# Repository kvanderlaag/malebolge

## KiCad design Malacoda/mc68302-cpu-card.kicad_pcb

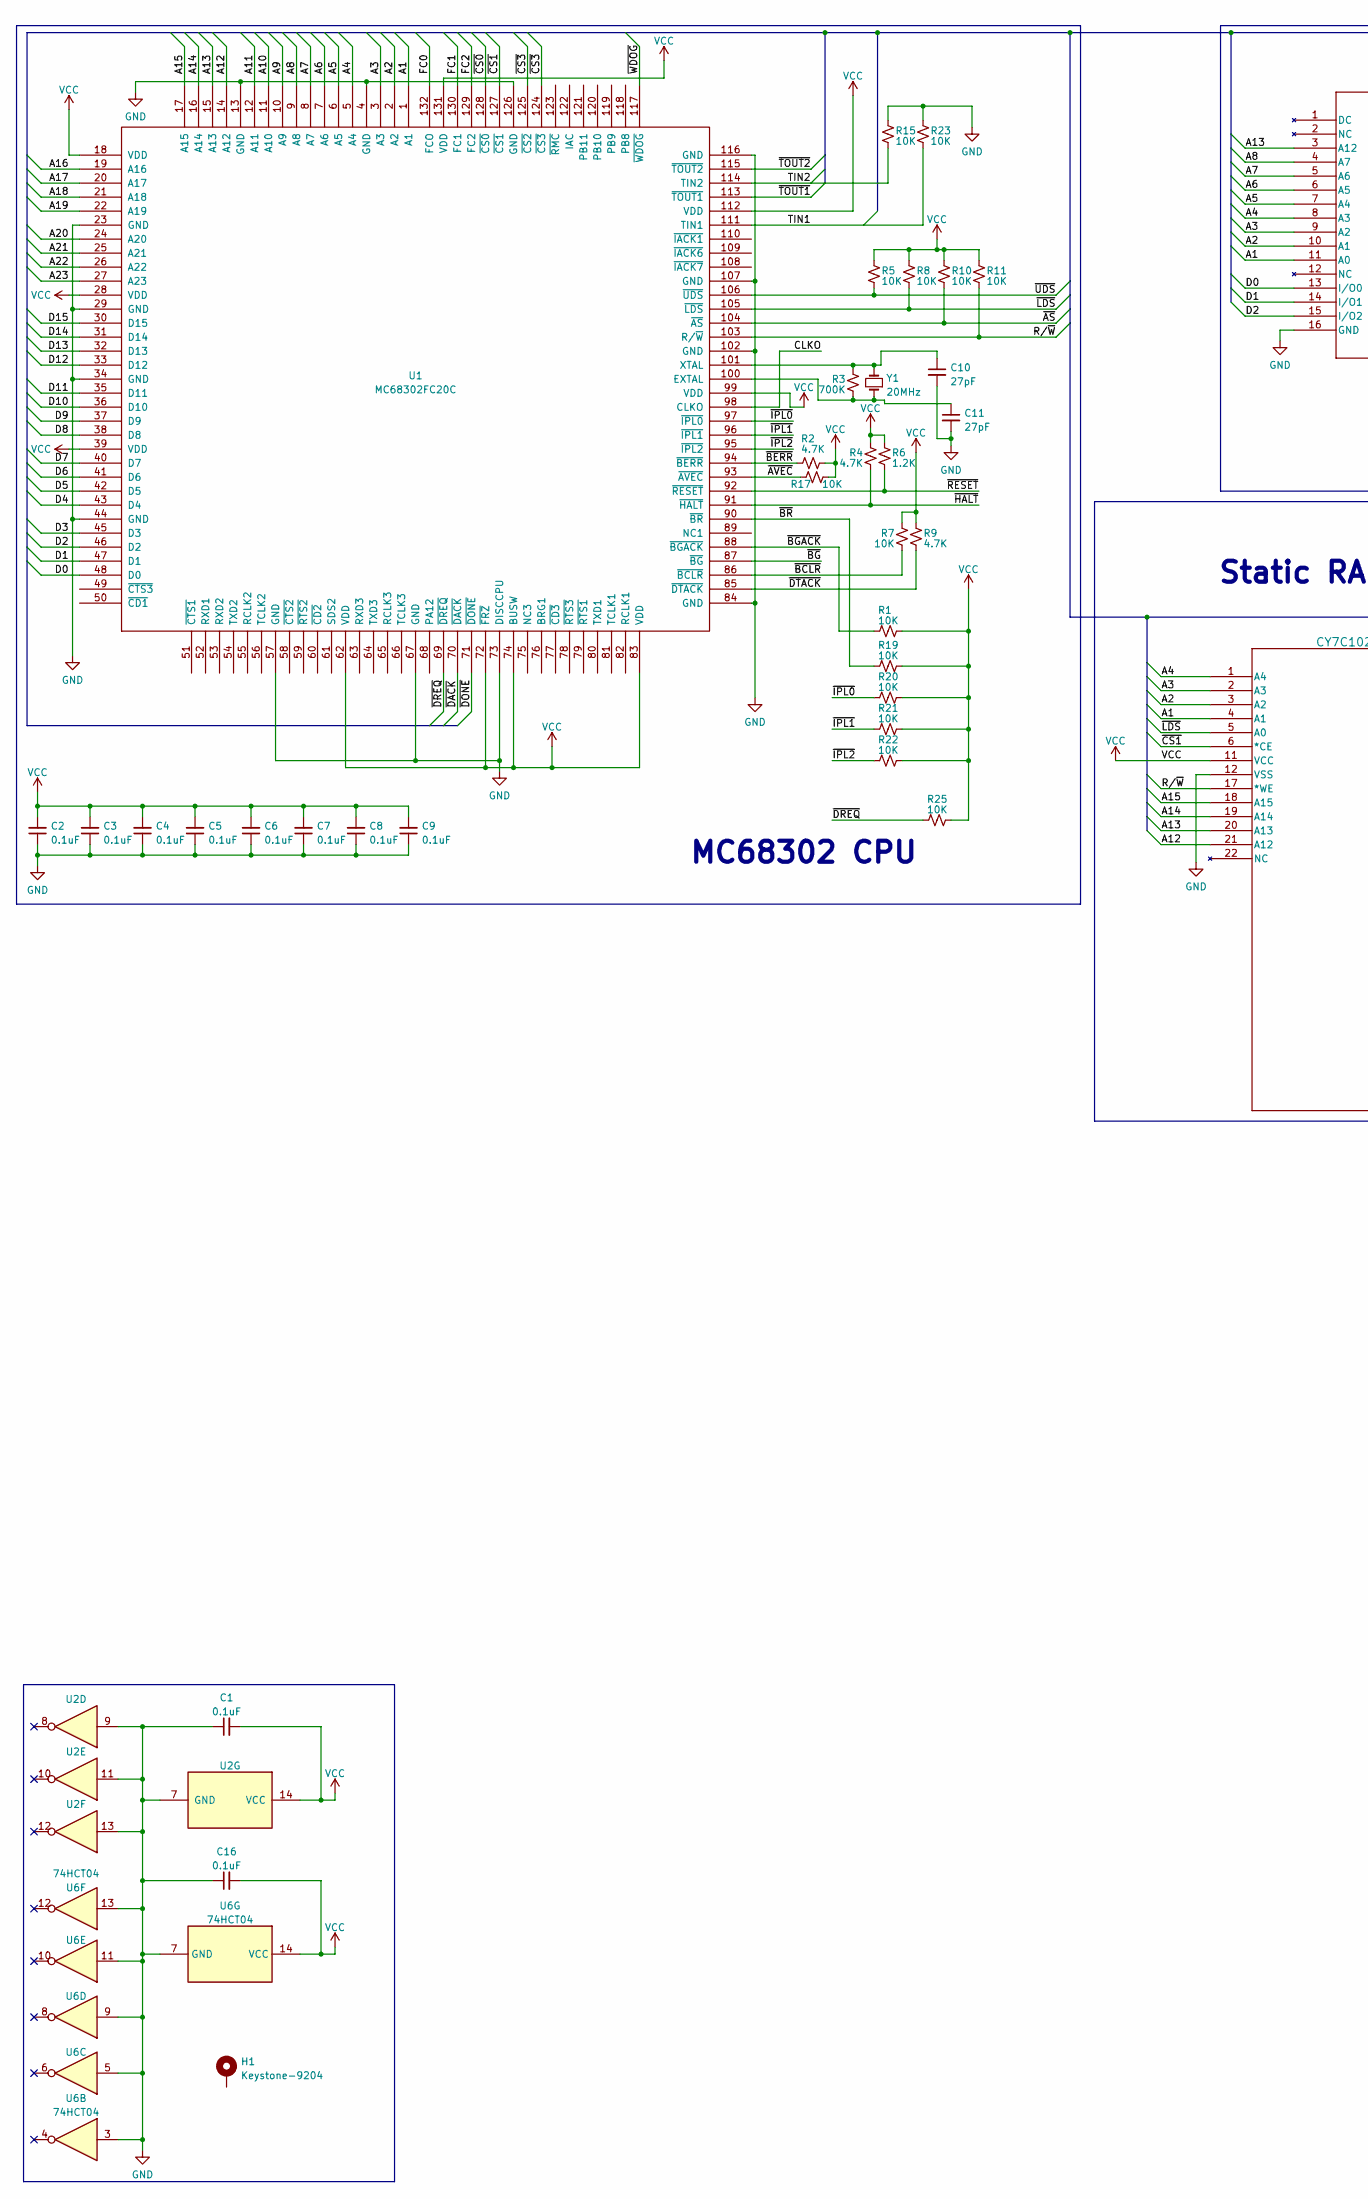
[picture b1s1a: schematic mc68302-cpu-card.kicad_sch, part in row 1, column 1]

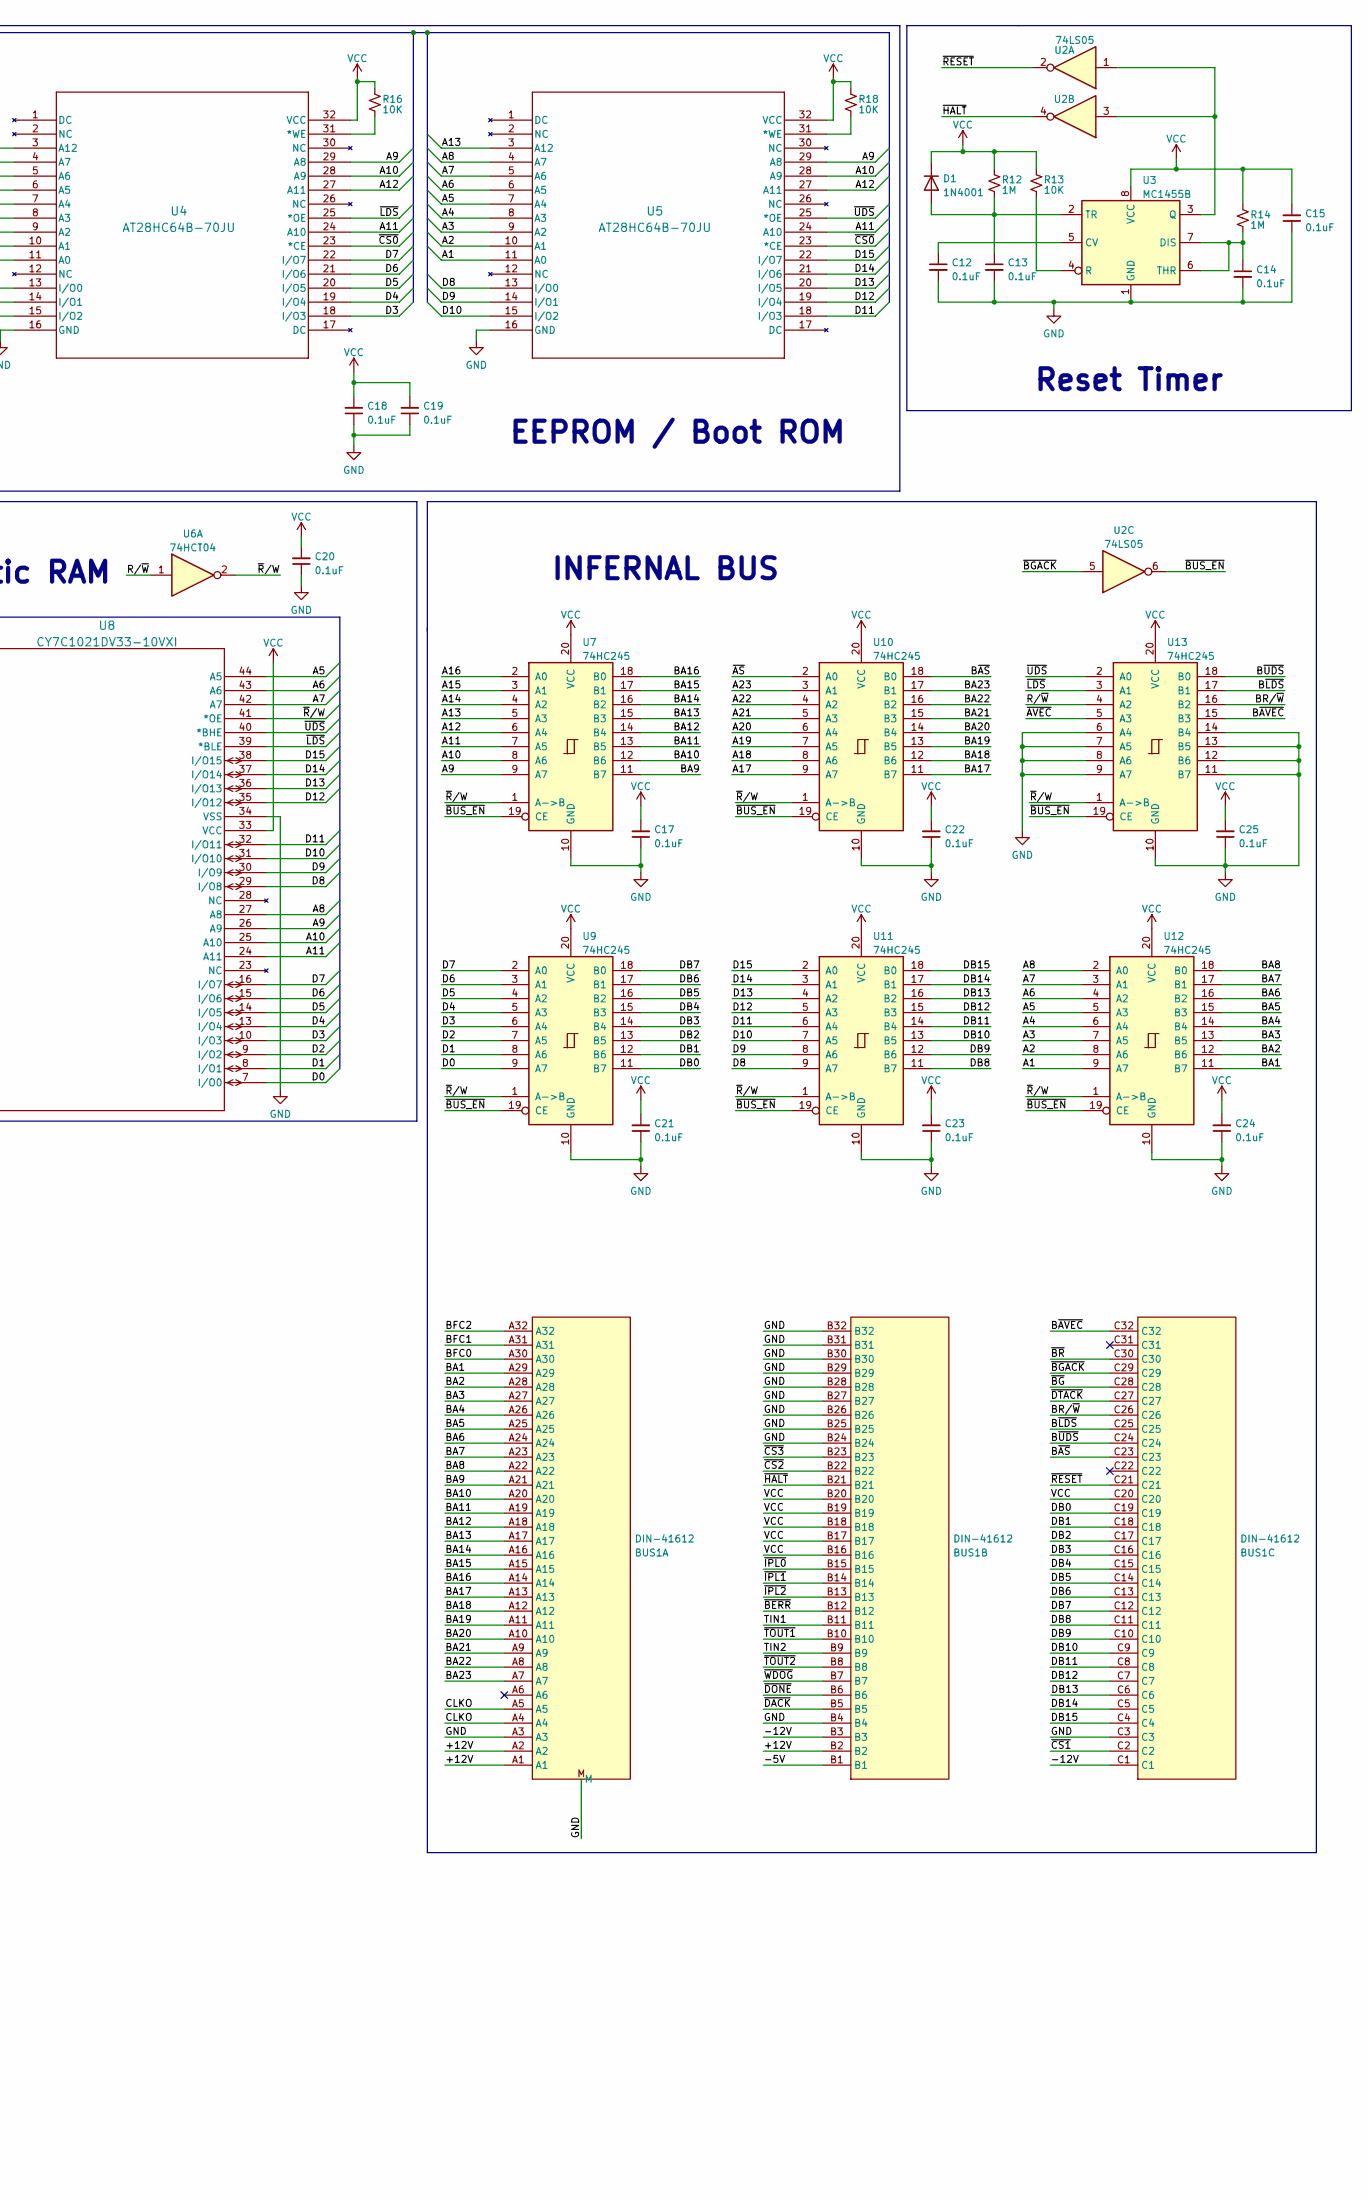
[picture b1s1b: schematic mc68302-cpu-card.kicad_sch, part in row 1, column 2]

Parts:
BUS1: DIN-41612; CONN96_8609_94X8P5_AOS
C1, C2, C3, C4, C5, C6, C7, C8, C9, C12, C13, C14, C15, C16, C17, C18, C19, C20, C21, C22, C23, C24, C25: 0.1uF; C_0805_2012Metric
C10, C11: 27pF; C_0805_2012Metric
D1: 1N4001; D_SMB
H1: Keystone-9204
R1, R5, R7, R8, R10, R11, R13, R15, R16, R17, R18, R19, R20, R21, R22, R23, R25: 10K; R_0805_2012Metric
R2, R4, R9: 4.7K; R_0805_2012Metric
R3: 700K; R_0805_2012Metric
R6: 1.2K; R_0805_2012Metric
R12, R14: 1M; R_0805_2012Metric
U1: MC68302FC20C; QFP-132_24.13x24.13_Pitch0.64mm
U2: 74LS05; SOIC-14_3.9x8.7mm_P1.27mm
U3: MC1455B; SOIC-8_3.9x4.9mm_P1.27mm
U4, U5: AT28HC64B-70JU; AT28HC64B
U6: 74HCT04; SOIC-14_3.9x8.7mm_P1.27mm
U7, U9, U10, U11, U12, U13: 74HC245; SOIC-20W_7.5x12.8mm_P1.27mm
U8: CY7C1021DV33-10VXI; SOJ-44-M
Y1: 20MHz; Crystal_SMD_5032-2Pin_5.0x3.2mm

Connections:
/+12V: BUS1.A1, BUS1.A2, BUS1.B2
/-5V: BUS1.B1
/-12V: BUS1.B3, BUS1.C1
/A1: U1.1 (A1), U4.11 (A0), U5.11 (A0), U8.4 (A1), U12.9 (A7)
/A2: U1.2 (A2), U4.10 (A1), U5.10 (A1), U8.3 (A2), U12.8 (A6)
/A3: U1.3 (A3), U4.9 (A2), U5.9 (A2), U8.2 (A3), U12.7 (A5)
/A4: U1.5 (A4), U4.8 (A3), U5.8 (A3), U8.1 (A4), U12.6 (A4)
/A5: U1.6 (A5), U4.7 (A4), U5.7 (A4), U8.44 (A5), U12.5 (A3)
/A6: U1.7 (A6), U4.6 (A5), U5.6 (A5), U8.43 (A6), U12.4 (A2)
/A7: U1.8 (A7), U4.5 (A6), U5.5 (A6), U8.42 (A7), U12.3 (A1)
/A8: U1.9 (A8), U4.4 (A7), U5.4 (A7), U8.27 (A8), U12.2 (A0)
/A9: U1.10 (A9), U4.29 (A8), U5.29 (A8), U7.9 (A7), U8.26 (A9)
/A10: U1.11 (A10), U4.28 (A9), U5.28 (A9), U7.8 (A6), U8.25 (A10)
/A11: U1.12 (A11), U4.24 (A10), U5.24 (A10), U7.7 (A5), U8.24 (A11)
/A12: U1.14 (A12), U4.27 (A11), U5.27 (A11), U7.6 (A4), U8.21 (A12)
/A13: U1.15 (A13), U4.3 (A12), U5.3 (A12), U7.5 (A3), U8.20 (A13)
/A14: U1.16 (A14), U7.4 (A2), U8.19 (A14)
/A15: U1.17 (A15), U7.3 (A1), U8.18 (A15)
/A16: U1.19 (A16), U7.2 (A0)
/A17: U1.20 (A17), U10.9 (A7)
/A18: U1.21 (A18), U10.8 (A6)
/A19: U1.22 (A19), U10.7 (A5)
/A20: U1.24 (A20), U10.6 (A4)
/A21: U1.25 (A21), U10.5 (A3)
/A22: U1.26 (A22), U10.4 (A2)
/A23: U1.27 (A23), U10.3 (A1)
/BA1: BUS1.A29, U12.11 (B7)
/BA2: BUS1.A28, U12.12 (B6)
/BA3: BUS1.A27, U12.13 (B5)
/BA4: BUS1.A26, U12.14 (B4)
/BA5: BUS1.A25, U12.15 (B3)
/BA6: BUS1.A24, U12.16 (B2)
/BA7: BUS1.A23, U12.17 (B1)
/BA8: BUS1.A22, U12.18 (B0)
/BA9: BUS1.A21, U7.11 (B7)
/BA10: BUS1.A20, U7.12 (B6)
/BA11: BUS1.A19, U7.13 (B5)
/BA12: BUS1.A18, U7.14 (B4)
/BA13: BUS1.A17, U7.15 (B3)
/BA14: BUS1.A16, U7.16 (B2)
/BA15: BUS1.A15, U7.17 (B1)
/BA16: BUS1.A14, U7.18 (B0)
/BA17: BUS1.A13, U10.11 (B7)
/BA18: BUS1.A12, U10.12 (B6)
/BA19: BUS1.A11, U10.13 (B5)
/BA20: BUS1.A10, U10.14 (B4)
/BA21: BUS1.A9, U10.15 (B3)
/BA22: BUS1.A8, U10.16 (B2)
/BA23: BUS1.A7, U10.17 (B1)
/BFC0: BUS1.A30
/BFC1: BUS1.A31
/BFC2: BUS1.A32
/BR/~W: BUS1.C26, U13.16 (B2)
/B~AS: BUS1.C23, U10.18 (B0)
/B~AVEC: BUS1.C32, U13.15 (B3)
/B~LDS: BUS1.C25, U13.17 (B1)
/B~UDS: BUS1.C24, U13.18 (B0)
/CLKO: BUS1.A4, BUS1.A5, U1.98 (CLKO)
/D0: U1.48 (D0), U4.13 (I/O0), U8.7 (I/O0), U9.9 (A7)
/D1: U1.47 (D1), U4.14 (I/O1), U8.8 (I/O1), U9.8 (A6)
/D2: U1.46 (D2), U4.15 (I/O2), U8.9 (I/O2), U9.7 (A5)
/D3: U1.45 (D3), U4.18 (I/O3), U8.10 (I/O3), U9.6 (A4)
/D4: U1.43 (D4), U4.19 (I/O4), U8.13 (I/O4), U9.5 (A3)
/D5: U1.42 (D5), U4.20 (I/O5), U8.14 (I/O5), U9.4 (A2)
/D6: U1.41 (D6), U4.21 (I/O6), U8.15 (I/O6), U9.3 (A1)
/D7: U1.40 (D7), U4.22 (I/O7), U8.16 (I/O7), U9.2 (A0)
/D8: U1.38 (D8), U5.13 (I/O0), U8.29 (I/O8), U11.9 (A7)
/D9: U1.37 (D9), U5.14 (I/O1), U8.30 (I/O9), U11.8 (A6)
/D10: U1.36 (D10), U5.15 (I/O2), U8.31 (I/O10), U11.7 (A5)
/D11: U1.35 (D11), U5.18 (I/O3), U8.32 (I/O11), U11.6 (A4)
/D12: U1.33 (D12), U5.19 (I/O4), U8.35 (I/O12), U11.5 (A3)
/D13: U1.32 (D13), U5.20 (I/O5), U8.36 (I/O13), U11.4 (A2)
/D14: U1.31 (D14), U5.21 (I/O6), U8.37 (I/O14), U11.3 (A1)
/D15: U1.30 (D15), U5.22 (I/O7), U8.38 (I/O15), U11.2 (A0)
/DB0: BUS1.C19, U9.11 (B7)
/DB1: BUS1.C18, U9.12 (B6)
/DB2: BUS1.C17, U9.13 (B5)
/DB3: BUS1.C16, U9.14 (B4)
/DB4: BUS1.C15, U9.15 (B3)
/DB5: BUS1.C14, U9.16 (B2)
/DB6: BUS1.C13, U9.17 (B1)
/DB7: BUS1.C12, U9.18 (B0)
/DB8: BUS1.C11, U11.11 (B7)
/DB9: BUS1.C10, U11.12 (B6)
/DB10: BUS1.C9, U11.13 (B5)
/DB11: BUS1.C8, U11.14 (B4)
/DB12: BUS1.C7, U11.15 (B3)
/DB13: BUS1.C6, U11.16 (B2)
/DB14: BUS1.C5, U11.17 (B1)
/DB15: BUS1.C4, U11.18 (B0)
/FC0: U1.132 (FCO)
/FC1: U1.130 (FC1)
/FC2: U1.129 (FC2)
/R/~W: R11.2, U1.103 (R/~W), U6.1, U8.17 (*WE), U13.4 (A2)
/TIN1: BUS1.B11, R23.2, U1.111 (TIN1)
/TIN2: BUS1.B9, R15.2, U1.114 (TIN2)
/~AS: R10.2, U1.104 (~AS), U10.2 (A0)
/~AVEC: R17.1, U1.93 (~AVEC), U13.5 (A3)
/~BCLR: R7.2, U1.86 (~BCLR)
/~BERR: BUS1.B12, R2.1, U1.94 (~BERR)
/~BGACK: BUS1.C29, R1.1, U1.88 (~BGACK), U2.5
/~BG: BUS1.C28, U1.87 (~BG)
/~BR: BUS1.C30, R19.1, U1.90 (~BR)
/~BUS_EN: U2.6, U7.19 (CE), U9.19 (CE), U10.19 (CE), U11.19 (CE), U12.19 (CE), U13.19 (CE)
/~CS0: U1.128 (~CS0), U4.23 (*CE), U5.23 (*CE)
/~CS1: BUS1.C2, U1.127 (~CS1), U8.6 (*CE)
/~CS2: BUS1.B22
/~CS3: BUS1.B23, U1.124 (~CS3), U1.125 (~CS2)
/~DACK: BUS1.B5, U1.70 (~DACK)
/~DONE: BUS1.B6, U1.71 (~DONE)
/~DREQ: R25.1, U1.69 (~DREQ)
/~DTACK: BUS1.C27, R9.2, U1.85 (~DTACK)
/~HALT: BUS1.B21, R4.2, U1.91 (~HALT), U2.4
/~IPL0: BUS1.B15, R20.1, U1.97 (~IPL0)
/~IPL1: BUS1.B14, R21.1, U1.96 (~IPL1)
/~IPL2: BUS1.B13, R22.1, U1.95 (~IPL2)
/~LDS: R8.2, U1.105 (~LDS), U4.25 (*OE), U8.5 (A0), U8.39 (*BLE), U13.3 (A1)
/~RESET: BUS1.C21, R6.2, U1.92 (~RESET), U2.2
/~R/W: U6.2, U7.1 (A->B), U8.41 (*OE), U9.1 (A->B), U10.1 (A->B), U11.1 (A->B), U12.1 (A->B), U13.1 (A->B)
/~TOUT1: BUS1.B10, U1.113 (~TOUT1)
/~TOUT2: BUS1.B8, U1.115 (~TOUT2)
/~UDS: R5.2, U1.106 (~UDS), U5.25 (*OE), U8.40 (*BHE), U13.2 (A0)
/~WDOG: BUS1.B7, U1.117 (~WDOG)
GND: BUS1.A3, BUS1.B4, BUS1.B24, BUS1.B25, BUS1.B26, BUS1.B27, BUS1.B28, BUS1.B29, BUS1.B30, BUS1.B31, BUS1.B32, BUS1.C3, BUS1.M, C1.1, C2.1, C3.1, C4.1, C5.1, C6.1, C7.1, C8.1, C9.1, C10.2, C11.2, C12.2, C13.2, C14.2, C15.1, C16.1, C17.1, C18.1, C19.1, C20.1, C21.1, C22.1, C23.1, C24.1, C25.1, R15.1, R23.1, U1.4 (GND), U1.13 (GND), U1.23 (GND), U1.29 (GND), U1.34 (GND), U1.44 (GND), U1.57 (GND), U1.67 (GND), U1.73 (DISCCPU), U1.84 (GND), U1.102 (GND), U1.107 (GND), U1.116 (GND), U1.126 (GND), U2.7 (GND), U2.9, U2.11, U2.13, U3.1 (GND), U4.16 (GND), U5.16 (GND), U6.3, U6.5, U6.7 (GND), U6.9, U6.11, U6.13, U7.10 (GND), U8.12 (VSS), U8.34 (VSS), U9.10 (GND), U10.10 (GND), U11.10 (GND), U12.10 (GND), U13.6 (A4), U13.7 (A5), U13.8 (A6), U13.9 (A7), U13.10 (GND), U13.11 (B7), U13.12 (B6), U13.13 (B5), U13.14 (B4)
unnamed: C10.1, R3.1, U1.101 (XTAL), Y1.2
unnamed: C11.1, R3.2, U1.100 (EXTAL), Y1.1
unnamed: C12.1, U3.5 (CV)
unnamed: C13.1, D1.2 (A), R12.2, U3.2 (TR)
unnamed: C14.1, R14.2, U3.6 (THR), U3.7 (DIS)
unnamed: R13.2, U3.4 (R)
unnamed: R16.2, U4.31 (*WE)
unnamed: R18.2, U5.31 (*WE)
unnamed: U2.1, U2.3, U3.3 (Q)
VCC: BUS1.B16, BUS1.B17, BUS1.B18, BUS1.B19, BUS1.B20, BUS1.C20, C1.2, C2.2, C3.2, C4.2, C5.2, C6.2, C7.2, C8.2, C9.2, C15.2, C16.2, C17.2, C18.2, C19.2, C20.2, C21.2, C22.2, C23.2, C24.2, C25.2, D1.1 (K), R1.2, R2.2, R4.1, R5.1, R6.1, R7.1, R8.1, R9.1, R10.1, R11.1, R12.1, R13.1, R14.1, R16.1, R17.2, R18.1, R19.2, R20.2, R21.2, R22.2, R25.2, U1.18 (VDD), U1.28 (VDD), U1.39 (VDD), U1.62 (VDD), U1.72 (~FRZ), U1.74 (BUSW), U1.83 (VDD), U1.99 (VDD), U1.112 (VDD), U1.131 (VDD), U2.14 (VCC), U3.8 (VCC), U4.32 (VCC), U5.32 (VCC), U6.14 (VCC), U7.20 (VCC), U8.11 (VCC), U8.33 (VCC), U9.20 (VCC), U10.20 (VCC), U11.20 (VCC), U12.20 (VCC), U13.20 (VCC)

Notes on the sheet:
Static RAM
INFERNAL BUS
EEPROM / Boot ROM
Reset Timer
MC68302 CPU

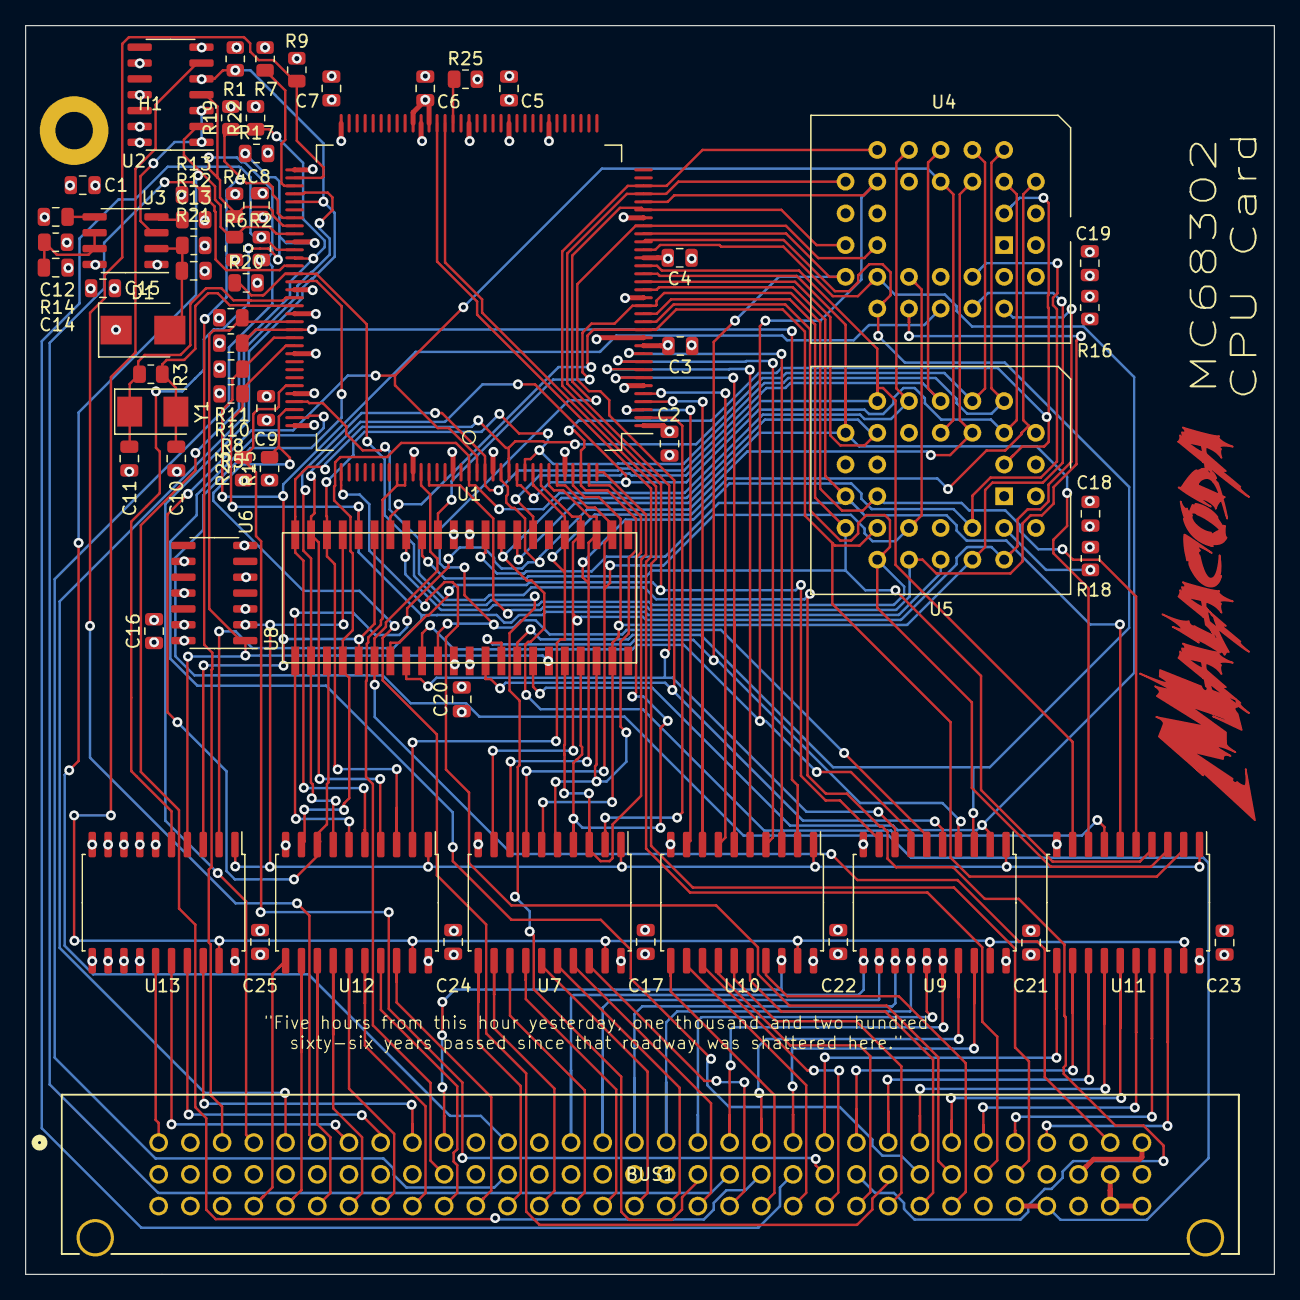
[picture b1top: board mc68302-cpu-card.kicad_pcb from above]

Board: 4 copper layers, 100.0 x 100.0 mm, 66 parts (0 on the bottom side), 126 nets.
